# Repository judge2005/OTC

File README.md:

# OTC

KiCAD project for the [One Tube Clock](http://www.nixies.us/projects/one-tube-clock/) Nixie clock:

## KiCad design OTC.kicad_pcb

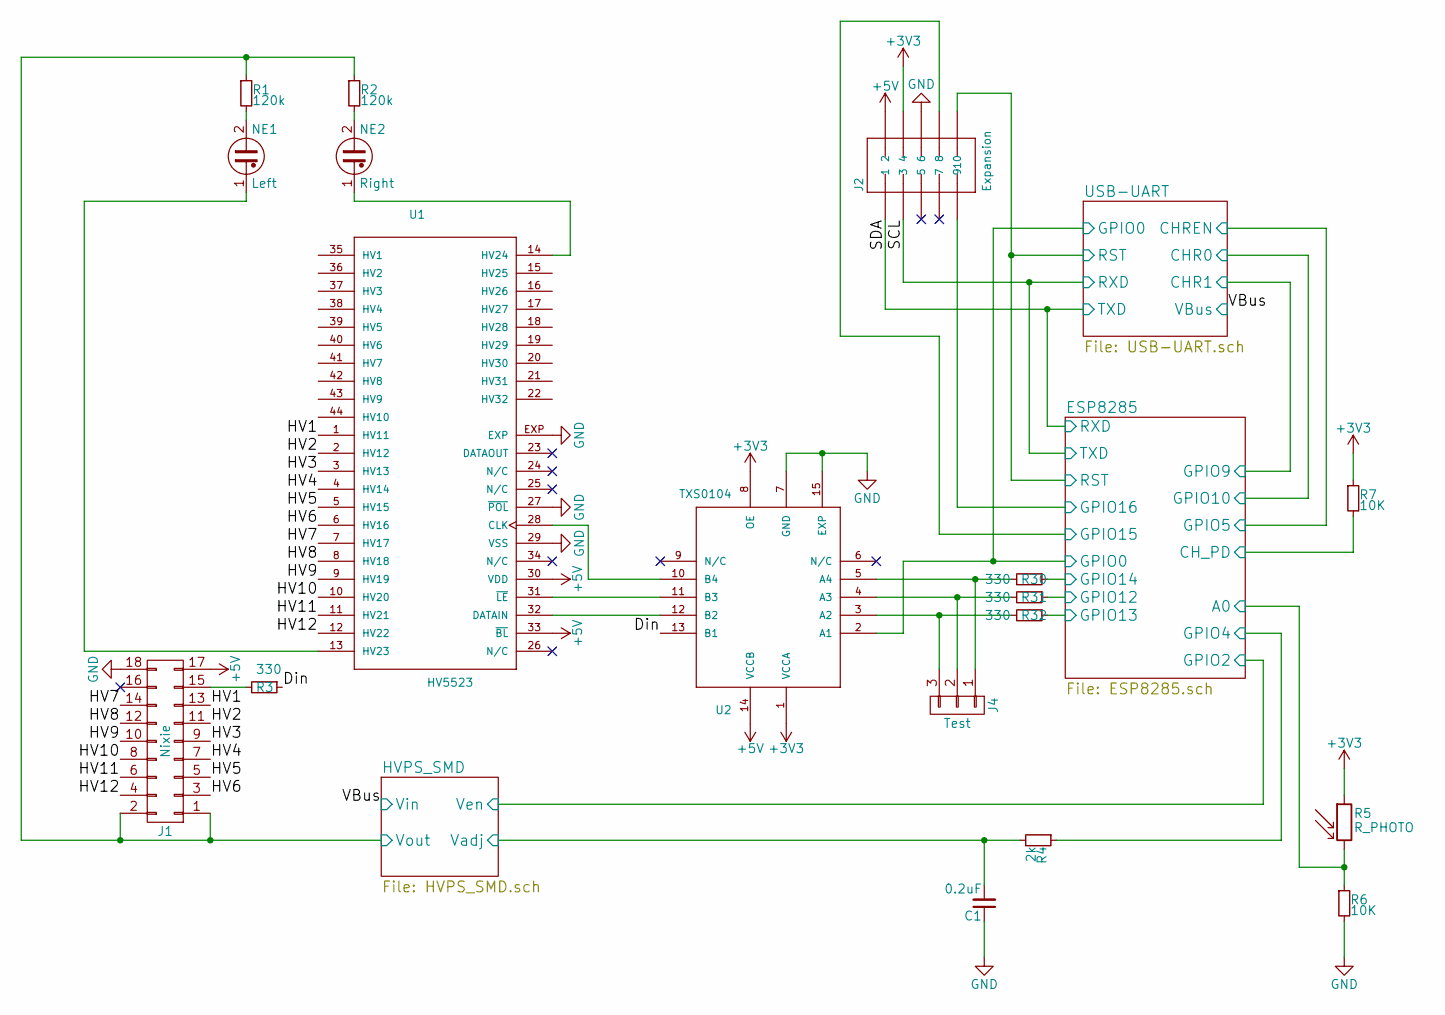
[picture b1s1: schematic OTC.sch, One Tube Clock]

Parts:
C1: 0.2uF; C_0603
J1: Nixie; Pin_Header_Straight_2x09_Pitch2.54mm
J2: Expansion; Pin_Header_Straight_2x05_Pitch2.54mm
J4: Test; SparkFun-Connectors-1X03_NO_SILK
NE1: Left; nixiemisc-THT-100-35
NE2: Right; nixiemisc-THT-100-35
R1, R2: 120k; R_0603
R3, R30, R31, R32: 330; R_0603
R4: 2k; R_0603
R5: R_PHOTO; nixiemisc-THT-150-35
R6, R7: 10K; R_0603
U1: HV5523; nixiemisc-QFN-44-7X7
U2: TXS0104; nixiemisc-VQFN-14

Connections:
+3V3: J2.4, R5.1, R7.1, U2.1 (VCCA), U2.8 (OE); also elsewhere on the board
+5V: J1.17, J2.2, U1.30 (VDD), U1.33 (~BL), U2.14 (VCCB); also elsewhere on the board
/Din: R3.1, U2.13 (B1)
/ESP8285/A0: R5.2, R6.1; also elsewhere on the board
/ESP8285/CH_PD: R7.2; also elsewhere on the board
/ESP8285/GPIO0: U2.2 (A1); also elsewhere on the board
/ESP8285/GPIO4: R4.1; also elsewhere on the board
/ESP8285/GPIO12: R31.1; also elsewhere on the board
/ESP8285/GPIO13: R32.1; also elsewhere on the board
/ESP8285/GPIO14: R30.1; also elsewhere on the board
/ESP8285/GPIO15: J2.8; also elsewhere on the board
/ESP8285/GPIO16: J2.9; also elsewhere on the board
/ESP8285/RST: J2.10; also elsewhere on the board
/HV1: J1.13, U1.1 (HV11)
/HV2: J1.11, U1.2 (HV12)
/HV3: J1.9, U1.3 (HV13)
/HV4: J1.7, U1.4 (HV14)
/HV5: J1.5, U1.5 (HV15)
/HV6: J1.3, U1.6 (HV16)
/HV7: J1.14, U1.7 (HV17)
/HV8: J1.12, U1.8 (HV18)
/HV9: J1.10, U1.9 (HV19)
/HV10: J1.8, U1.10 (HV20)
/HV11: J1.6, U1.11 (HV21)
/HV12: J1.4, U1.12 (HV22)
/HVPS_SMD/Vadj: C1.2, R4.2; also elsewhere on the board
/SCL: J2.3; also elsewhere on the board
/SDA: J2.1; also elsewhere on the board
GND: C1.1, J1.18, J2.6, R6.2, U1.27 (~POL), U1.29 (VSS), U1.EXP, U2.7 (GND), U2.15 (EXP); also elsewhere on the board
unnamed: J1.15, R3.2
unnamed: J4.1, R30.2, U2.5 (A4)
unnamed: J4.2, R31.2, U2.4 (A3)
unnamed: J4.3, R32.2, U2.3 (A2)
unnamed: NE1.1, U1.13 (HV23)
unnamed: NE1.2, R1.2
unnamed: NE2.1, U1.14 (HV24)
unnamed: NE2.2, R2.2
unnamed: U1.28 (CLK), U2.10 (B4)
unnamed: U1.31 (~LE), U2.11 (B3)
unnamed: U1.32 (DATAIN), U2.12 (B2)
Vout: J1.1, J1.2, R1.1, R2.1; also elsewhere on the board

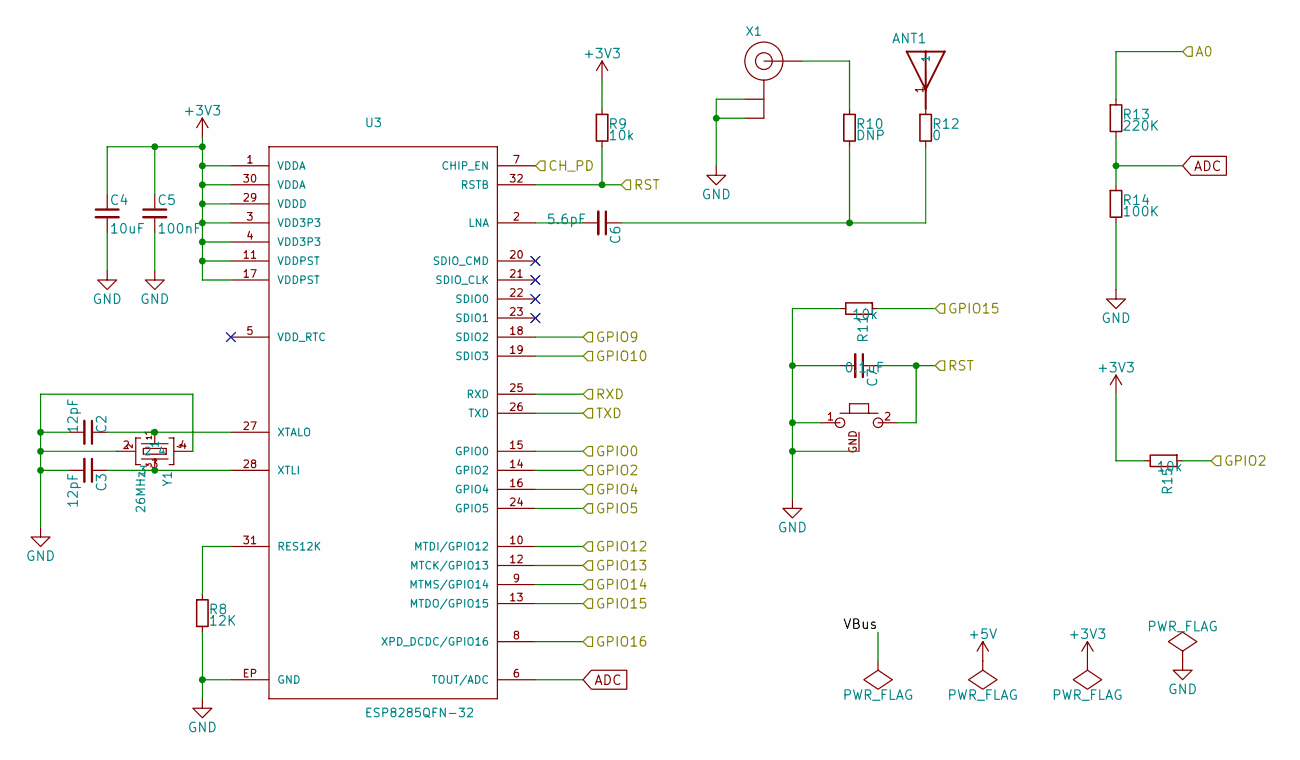
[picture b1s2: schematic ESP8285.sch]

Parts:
ANT1: 2450AT18B100E; ANT_2450AT18B100E
C2, C3: 12pF; C_0603
C4: 10uF; C_0603
C5: 100nF; C_0603
C6: 5.6pF; C_0603
C7: 0.1uF; C_0603
K1: RST; nixiemisc-B3U-1100P(M)
R8: 12K; R_0603
R9, R11, R15: 10k; R_0603
R10: DNP; SparkFun-Resistors-0603
R12: 0; SparkFun-Resistors-0603
R13: 220K; R_0603
R14: 100K; R_0603
U3: ESP8285QFN-32; nixiemisc-QFN-32
X1: ANTENNA_U.FL; adafruit-U.FL
Y1: 26MHz; nixiemisc-CRYSTAL2.0X1.6

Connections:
+3V3: C4.1, C5.1, R9.1, R15.2, U3.1 (VDDA), U3.3 (VDD3P3), U3.4 (VDD3P3), U3.11 (VDDPST), U3.17 (VDDPST), U3.29 (VDDD), U3.30 (VDDA); also elsewhere on the board
/ESP8285/A0: R13.1; also elsewhere on the board
/ESP8285/CH_PD: U3.7 (CHIP_EN); also elsewhere on the board
/ESP8285/GPIO0: U3.15 (GPIO0); also elsewhere on the board
/ESP8285/GPIO2: R15.1, U3.14 (GPIO2); also elsewhere on the board
/ESP8285/GPIO4: U3.16 (GPIO4); also elsewhere on the board
/ESP8285/GPIO12: U3.10 (MTDI/GPIO12); also elsewhere on the board
/ESP8285/GPIO13: U3.12 (MTCK/GPIO13); also elsewhere on the board
/ESP8285/GPIO14: U3.9 (MTMS/GPIO14); also elsewhere on the board
/ESP8285/GPIO15: R11.1, U3.13 (MTDO/GPIO15); also elsewhere on the board
/ESP8285/GPIO16: U3.8 (XPD_DCDC/GPIO16); also elsewhere on the board
/ESP8285/RST: C7.1, K1.2, R9.2, U3.32 (RSTB); also elsewhere on the board
/SCL: U3.26 (TXD); also elsewhere on the board
/SDA: U3.25 (RXD); also elsewhere on the board
/USB-UART/CHR0: U3.19 (SDIO3); also elsewhere on the board
/USB-UART/CHR1: U3.18 (SDIO2); also elsewhere on the board
/USB-UART/CHREN: U3.24 (GPIO5); also elsewhere on the board
ADC: R13.2, R14.1, U3.6 (TOUT/ADC)
GND: C2.2, C3.2, C4.2, C5.2, C7.2, K1.1, K1.GND, R8.2, R11.2, R14.2, U3.EP (GND), X1.1 (GND), X1.2 (GND), Y1.2, Y1.4; also elsewhere on the board
unnamed: ANT1.1, R12.1
unnamed: C2.1, U3.27 (XTALO), Y1.1
unnamed: C3.1, U3.28 (XTLI), Y1.3
unnamed: C6.1, R10.2, R12.2
unnamed: C6.2, U3.2 (LNA)
unnamed: R8.1, U3.31 (RES12K)
unnamed: R10.1, X1.3 (SIGNAL)

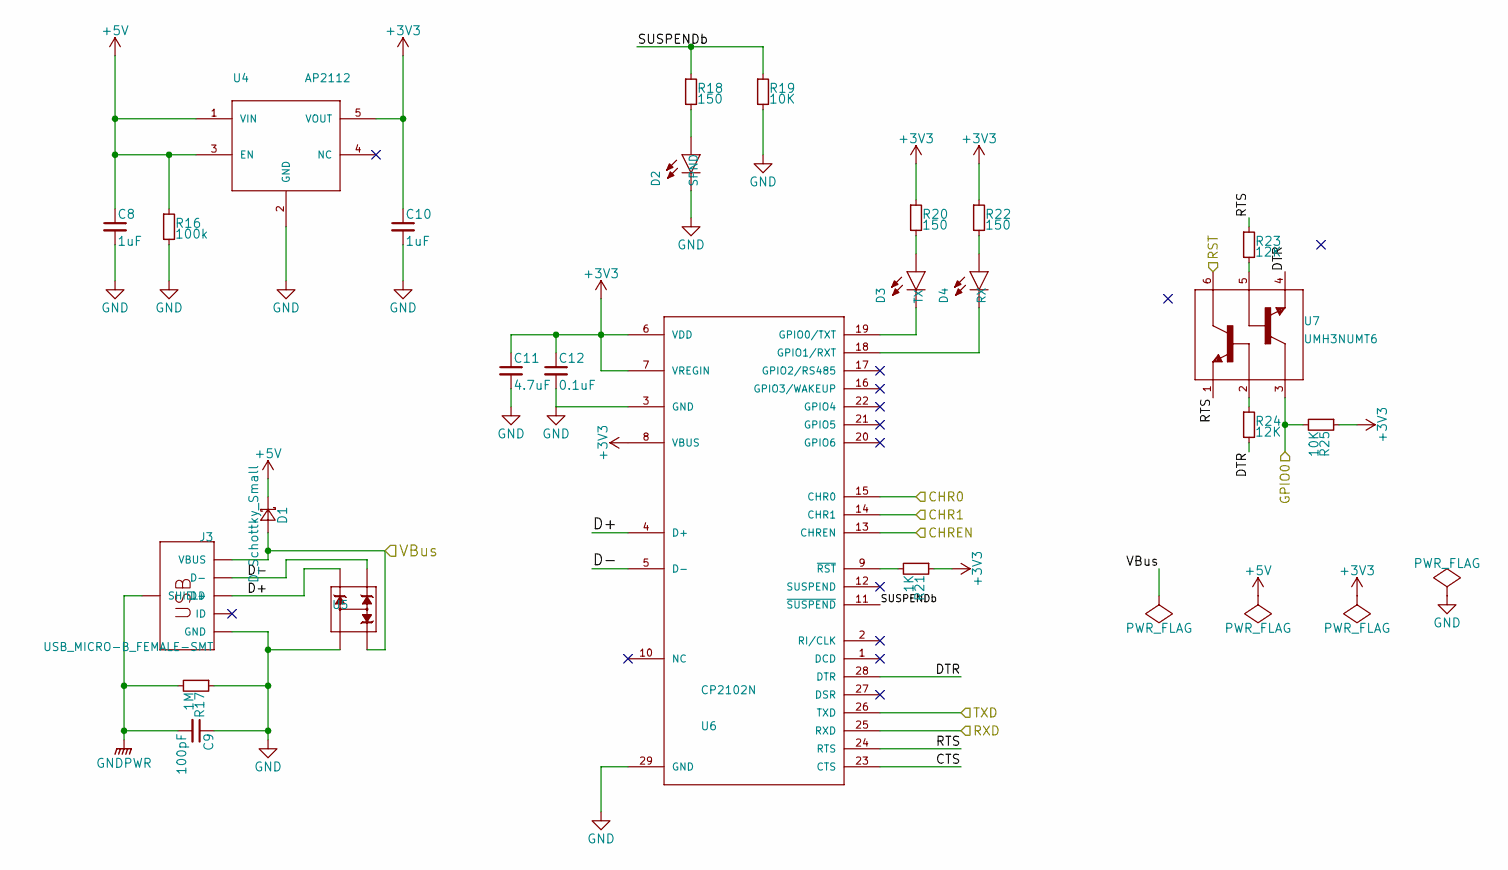
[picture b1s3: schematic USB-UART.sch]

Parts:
C8, C10: 1uF; C_0603
C9: 100pF; C_0603; Rating 1KV
C11: 4.7uF; C_0603
C12: 0.1uF; C_0603
D1: D_Schottky_Small; D_SOD-323_HandSoldering
D2: SPND; SparkFun-LED-LED-0603
D3: TX; SparkFun-LED-LED-0603
D4: RX; SparkFun-LED-LED-0603
J3: USB_MICRO-B_FEMALE-SMT; SparkFun-Connectors-USB-B-MICRO-SMD
R16: 100k; R_0603
R17: 1M; R_0603
R18, R20, R22: 150; R_0603_HandSoldering
R19, R25: 10K; R_0603
R21: 1K; R_0603
R23, R24: 12K; R_0603
U4: AP2112; nixiemisc-SOT25
U5: ESD; nixiemisc-SOT143
U6: CP2102N; nixiemisc-QFN28G_0.5-5X5MM
U7: UMH3NUMT6; nixiemisc-UMT6

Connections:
+3V3: C10.1, C11.1, C12.1, R20.1, R21.1, R22.1, R25.1, U4.5 (VOUT), U6.6 (VDD), U6.7 (VREGIN), U6.8 (VBUS); also elsewhere on the board
+5V: C8.1, D1.1 (K), R16.1, U4.1 (VIN), U4.3 (EN); also elsewhere on the board
/ESP8285/GPIO0: R25.2, U7.3 (C2); also elsewhere on the board
/ESP8285/RST: U7.6 (C1); also elsewhere on the board
/SCL: U6.25 (RXD); also elsewhere on the board
/SDA: U6.26 (TXD); also elsewhere on the board
/USB-UART/CHR0: U6.15 (CHR0); also elsewhere on the board
/USB-UART/CHR1: U6.14 (CHR1); also elsewhere on the board
/USB-UART/CHREN: U6.13 (CHREN); also elsewhere on the board
/USB-UART/CTS: U6.23 (CTS)
/USB-UART/D+: J3.D+, U5.4, U6.4 (D+)
/USB-UART/D-: J3.D-, U5.3, U6.5 (D-)
/USB-UART/DTR: R24.2, U6.28 (DTR), U7.4 (E2)
/USB-UART/RTS: R23.1, U6.24 (RTS), U7.1 (E1)
/USB-UART/SUSPENDb: R18.1, R19.1, U6.11 (~SUSPEND~)
GND: C8.2, C9.1, C10.2, C11.2, C12.2, D2.C, J3.GND, R16.2, R17.1, R19.2, U4.2 (GND), U5.1, U6.3 (GND), U6.29 (GND); also elsewhere on the board
GNDPWR: C9.2, J3.SHIE (SHIELD), R17.2
unnamed: D2.A, R18.2
unnamed: D3.A, R20.2
unnamed: D3.C, U6.19 (GPIO0/TXT)
unnamed: D4.A, R22.2
unnamed: D4.C, U6.18 (GPIO1/RXT)
unnamed: R21.2, U6.9 (~RST~)
unnamed: R23.2, U7.5 (B2)
unnamed: R24.1, U7.2 (B1)
Vin: D1.2 (A), J3.VBUS, U5.2; also elsewhere on the board

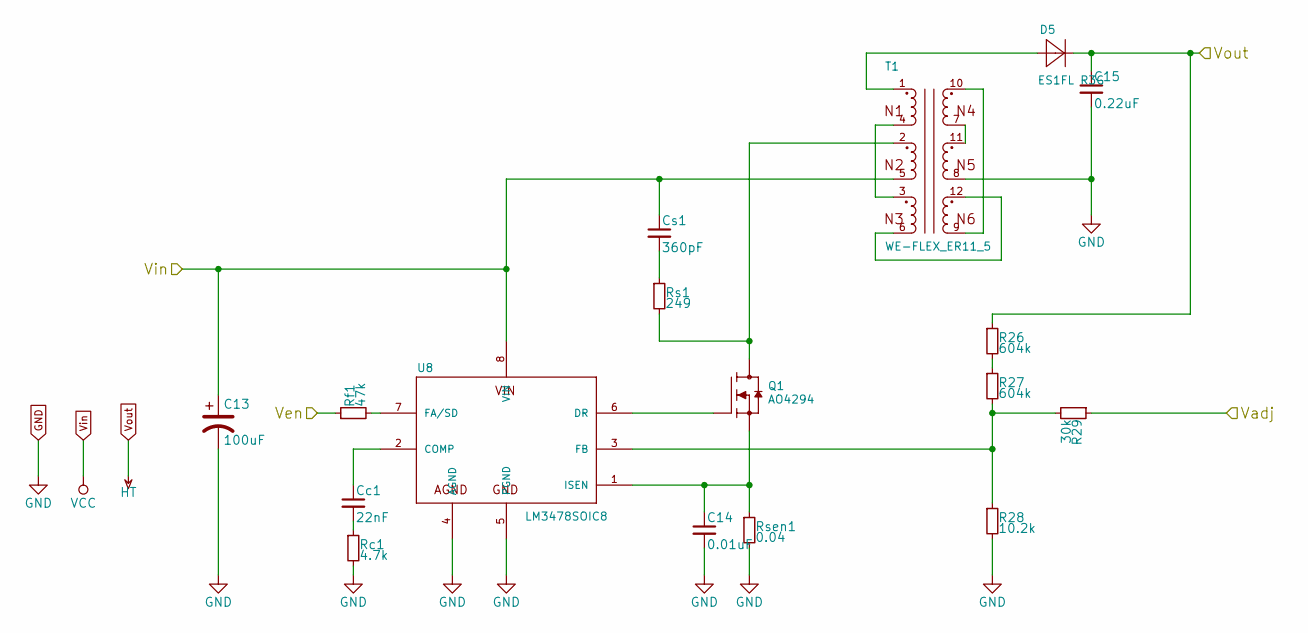
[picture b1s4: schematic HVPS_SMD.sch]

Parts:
C13: 100uF; C_1210
C14: 0.01uF; C_0603
C15: 0.22uF; C_1210
Cc1: 22nF; C_0603
Cs1: 360pF; C_0603
D5: ES1FL R3G; nixiemisc-DO-219AB
Q1: AO4294; nixiemisc-SO08
R26, R27: 604k; R_0805
R28: 10.2k; R_0603
R29: 30k; R_0603
Rc1: 4.7k; R_0805
Rf1: 47k; R_0805
Rs1: 249; R_1206
Rsen1: 0.04; R_2010
T1: WE-FLEX_ER11_5; nixiemisc-WE-FLEX_ER11_5
U8: LM3478SOIC8; nixiemisc-SO08

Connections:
/ESP8285/GPIO2: Rf1.1; also elsewhere on the board
/HVPS_SMD/Vadj: R29.1; also elsewhere on the board
GND: C13.2, C14.2, C15.2, R28.2, Rc1.2, Rsen1.2, T1.8 (5), U8.4 (AGND), U8.5 (PGND); also elsewhere on the board
unnamed: C14.1, Q1.1 (S), Q1.2 (S), Q1.3 (S), Rsen1.1, U8.1 (ISEN)
unnamed: Cc1.1, U8.2 (COMP)
unnamed: Cc1.2, Rc1.1
unnamed: Cs1.2, Rs1.1
unnamed: D5.A, T1.1
unnamed: Q1.4 (G), U8.6 (DR)
unnamed: Q1.5 (D), Q1.6 (D), Q1.7 (D), Q1.8 (D), Rs1.2, T1.2 (11)
unnamed: R26.2, R27.1
unnamed: R27.2, R28.1, R29.2, U8.3 (FB)
unnamed: Rf1.2, U8.7 (FA/SD)
unnamed: T1.3 (9), T1.4 (12)
unnamed: T1.9 (7), T1.10 (2)
unnamed: T1.7 (3), T1.11 (4)
unnamed: T1.6 (8), T1.12 (6)
Vin: C13.1, Cs1.1, T1.5 (10), U8.8 (VIN); also elsewhere on the board
Vout: C15.1, D5.C, R26.1; also elsewhere on the board

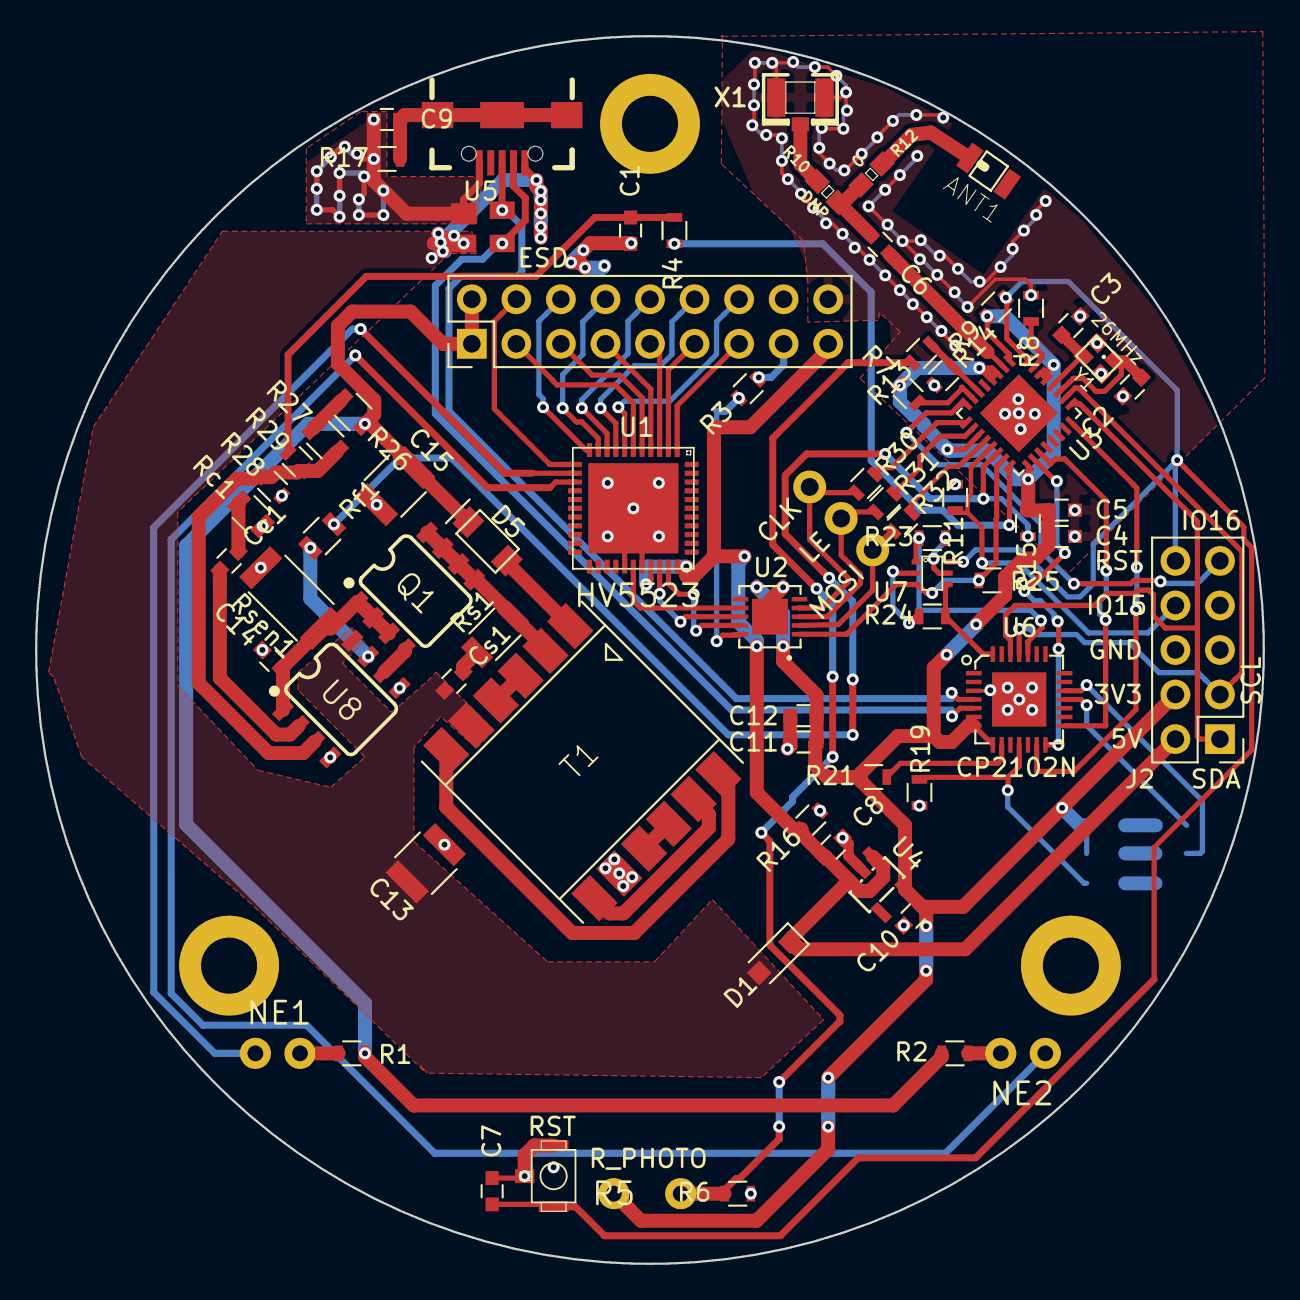
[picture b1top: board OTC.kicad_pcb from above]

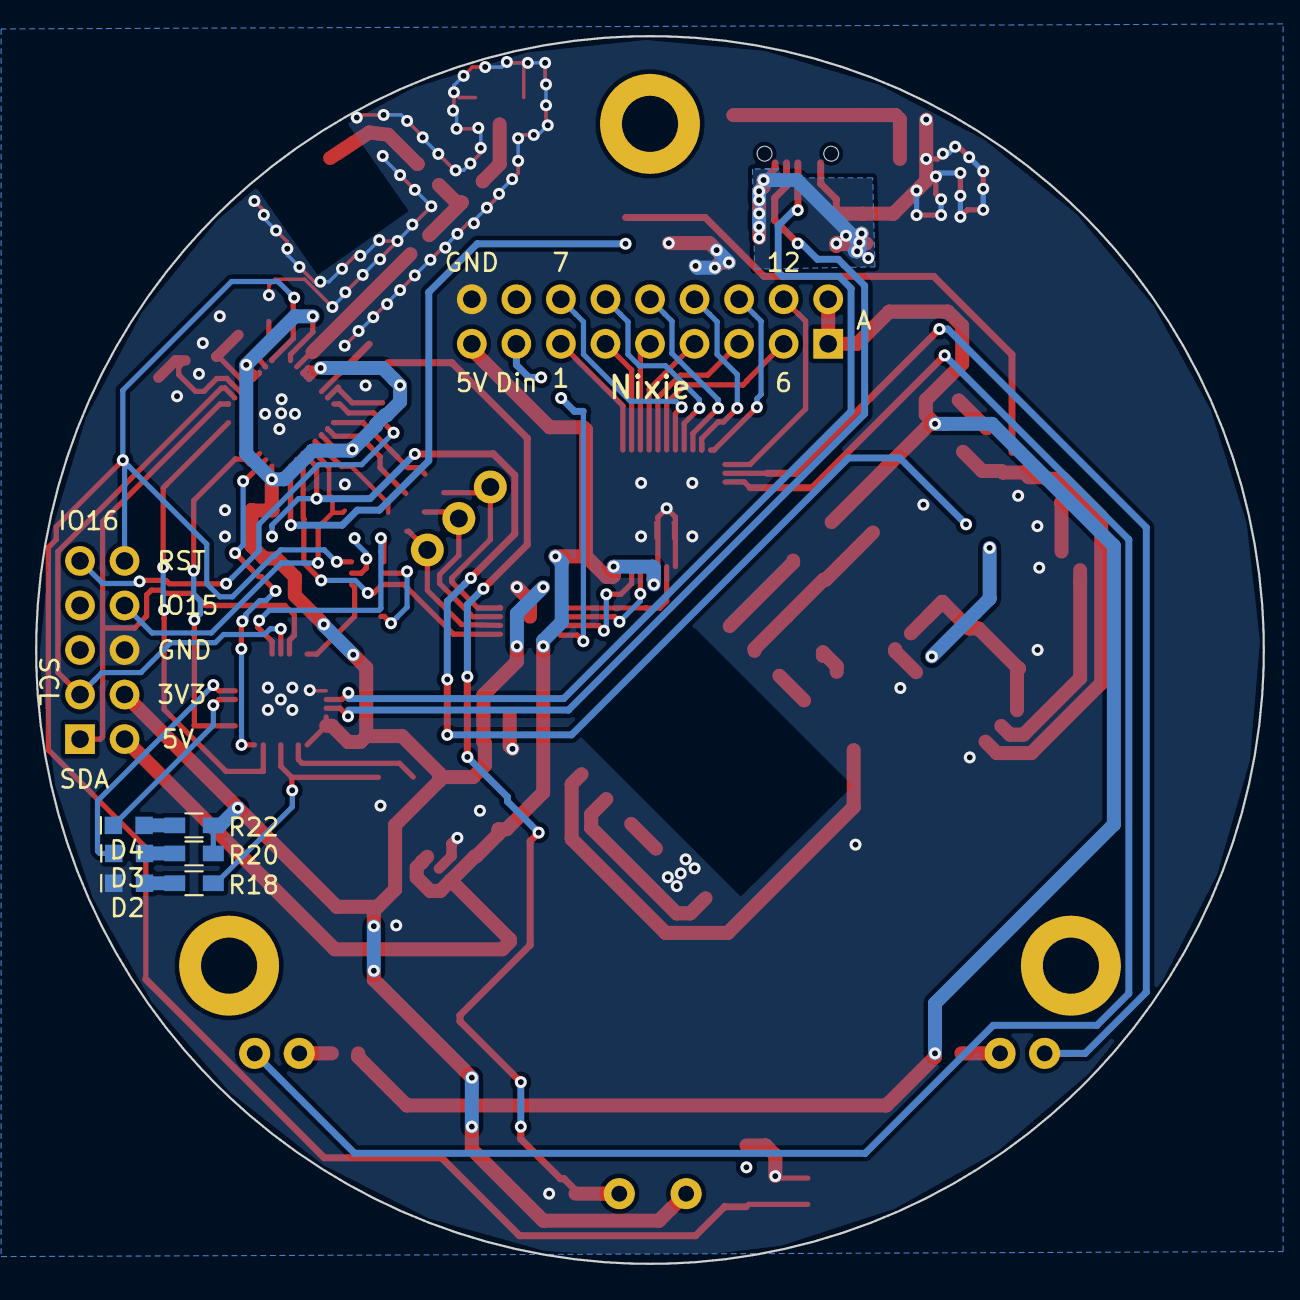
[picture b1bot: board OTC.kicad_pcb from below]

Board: 2 copper layers, 70.0 x 70.0 mm, 81 parts (6 on the bottom side), 82 nets.

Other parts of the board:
Mount1, Mount2, Mount3: MountingHole_3.2mm_M3_ISO7380_Pad
